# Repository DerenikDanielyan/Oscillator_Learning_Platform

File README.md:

# Oscillator_Learning_Platform
rev1

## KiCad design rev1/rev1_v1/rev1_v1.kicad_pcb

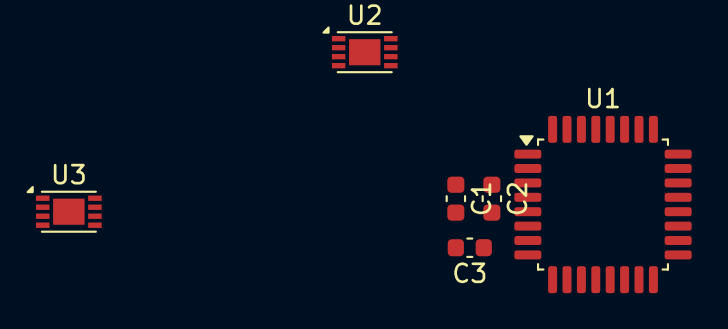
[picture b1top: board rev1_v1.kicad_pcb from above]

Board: 2 copper layers, 6 parts (0 on the bottom side), 7 nets, no tracks yet.

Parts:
C1, C3: 100n; C_0603_1608Metric
C2: 4.7uF; C_0603_1608Metric
U1: STM32G031K8Tx; LQFP-32_7x7mm_P0.8mm
U2: MCP4921-EMC; DFN-8-1EP_3x2mm_P0.5mm_EP1.75x1.45mm
U3: MCP6002-xMC; DFN-8-1EP_3x2mm_P0.5mm_EP1.75x1.45mm

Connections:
+3.3V: C1.1, C2.1, U1.4 (VDD), U2.1 (Vdd), U2.6 (Vref)
/CS: U1.11 (PA4), U2.2 (~CS)
/MCU_NRST: C3.1, U1.6 (PF2)
/MOSI: U1.9 (PA2), U2.4 (SDI)
/SCK: U1.8 (PA1), U2.3 (SCK)
GND: C1.2, C2.2, C3.2, U1.5 (VSS), U2.5 (~LDAC), U2.7 (Vss), U2.9 (PAD/Vss)
unnamed: U3.4 (V-), U3.9 (V-)

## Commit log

2026-01-29 Add KiCad gitignore
2026-01-29 MCU + DAC with passive LP filtering
